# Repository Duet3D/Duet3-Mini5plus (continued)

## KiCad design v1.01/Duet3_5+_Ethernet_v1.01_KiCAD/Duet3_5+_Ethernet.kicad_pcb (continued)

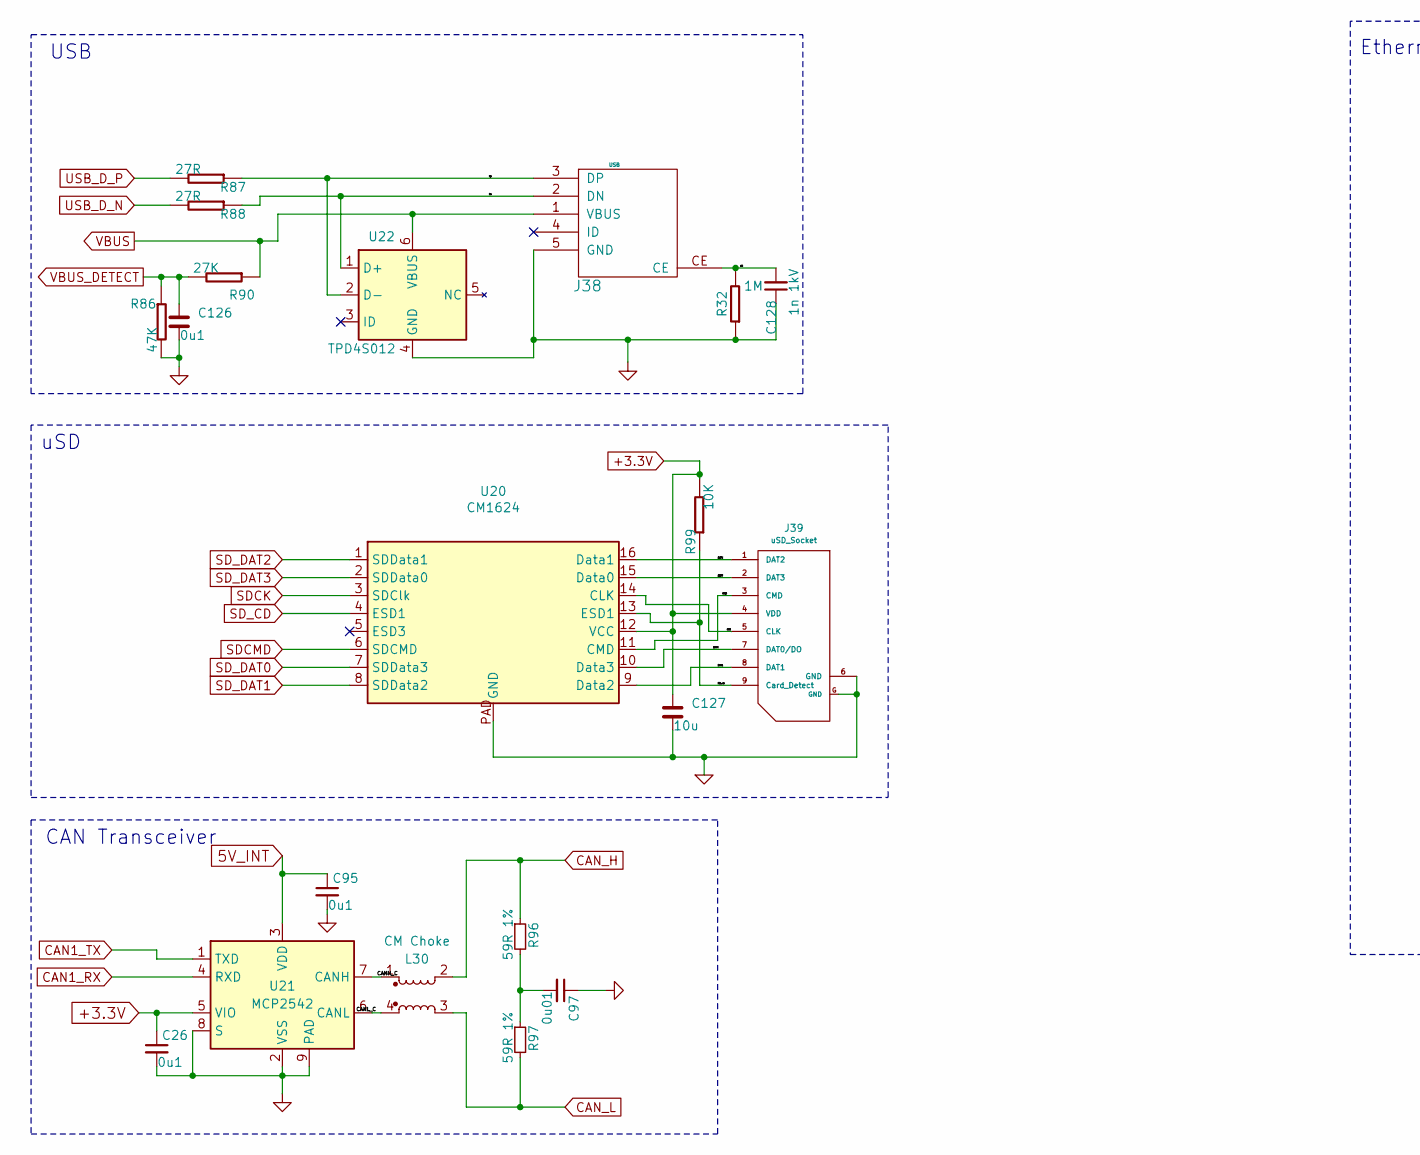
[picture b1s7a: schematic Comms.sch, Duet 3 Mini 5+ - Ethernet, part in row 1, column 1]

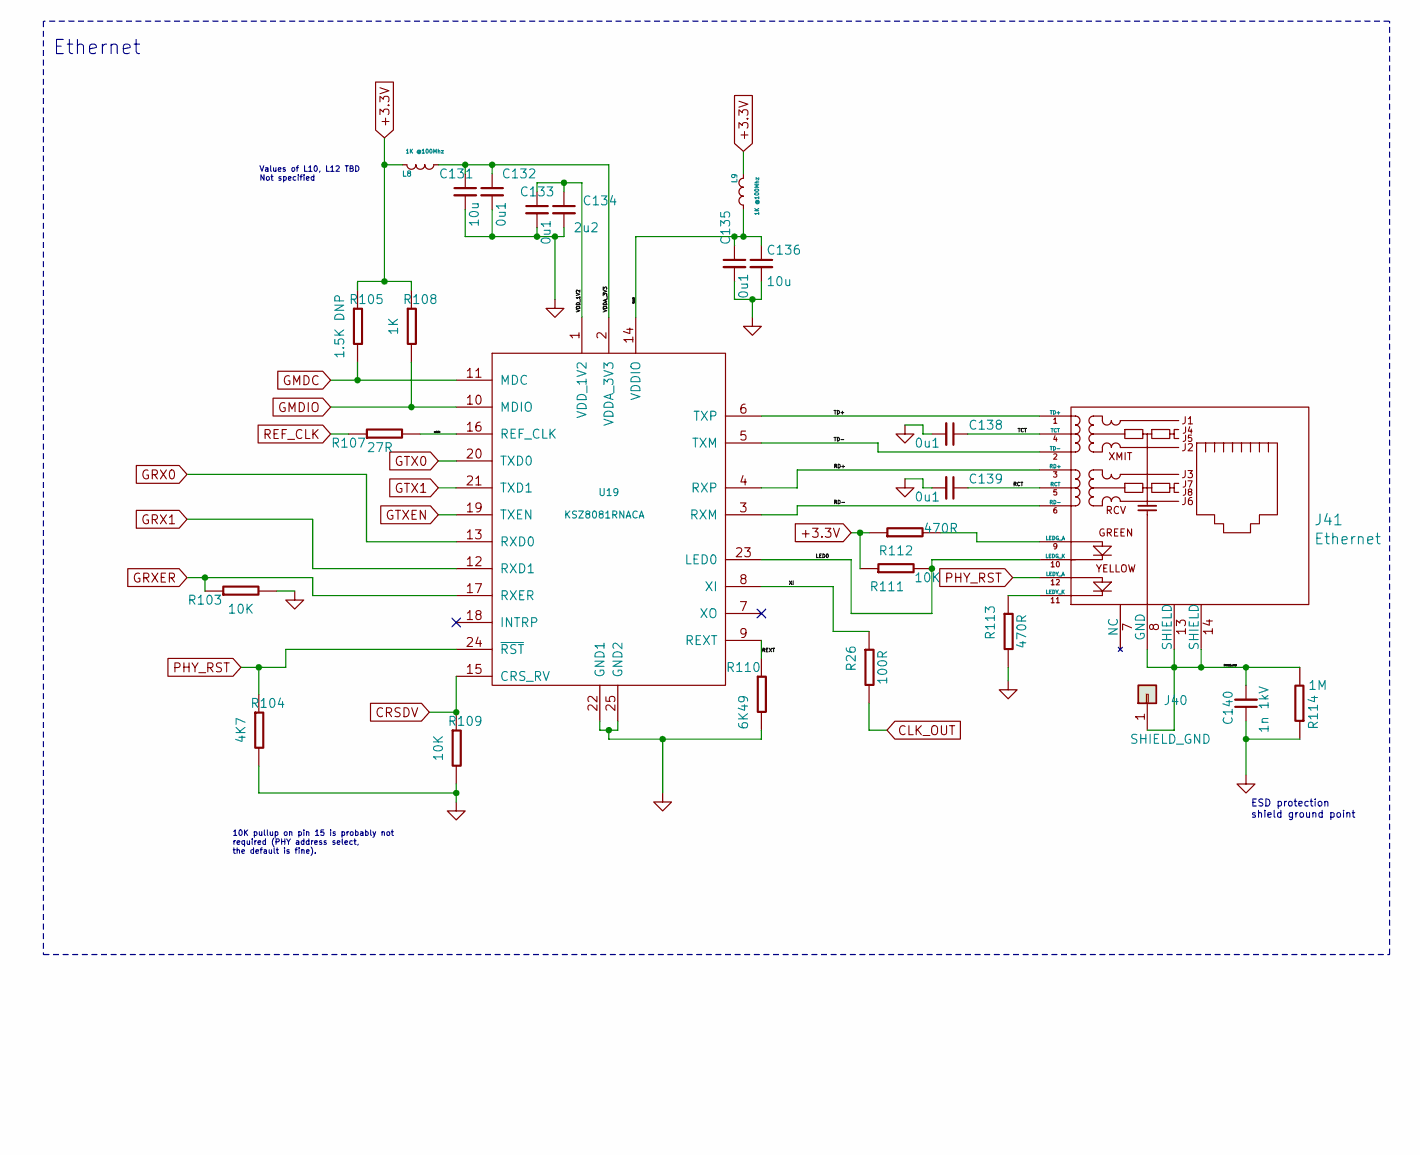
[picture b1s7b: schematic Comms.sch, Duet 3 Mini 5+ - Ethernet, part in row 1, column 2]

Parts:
C26, C95, C126, C132, C133, C135, C138, C139: 0u1; C_0402_1005Metric_Wbry; Part Number CL05A104KA5NNNC or similar
C97: 0u01; C_0402_1005Metric_Wbry; Part Number TMK105B7103KV-F
C127, C131, C136: 10u; C_0805_2012Metric; Part Number e.g CL21A106KQCLRNC
C128, C140: 1n 1kV; C_0805_2012Metric; Part Number CC0805KRX7RCBB102
C134: 2u2; C_0402_1005Metric_Wbry; Part Number LMK105BJ225KV-F or similar 10v+
J38: USB; uUSB_new; Part Number 10103594-0001LF
J39: uSD_Socket; uSD_SKT; Part Number 693071020811
J40: SHIELD_GND; 2.8mm_Spade_terminal; Part Number DNP - PC110D5
J41: Ethernet; RJ45+MAG; Part Number HR911105A
L8, L9: 1K @100Mhz; L_0603_1608Metric; Part Number BK1608HS102-T or PE-0603FB102ST or simi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
L30: CM Choke; Wurth_CM_Choke_744231121; Part Number 744231121 or SRF2012A-121YA
R26: 100R; R_0402_1005Metric_Wbry
R32, R114: 1M; R_0805_2012Metric; Part Number RMCF0805JT1M00
R86: 47K; R_0402_1005Metric_Wbry; Part Number RMCF0402FT47K0
R87, R88, R107: 27R; R_0402_1005Metric_Wbry; Part Number RC0402FR-0727RL
R90: 27K; R_0402_1005Metric_Wbry; Part Number RK73H1ETTP2702F
R96, R97: 59R 1%; R_0402_1005Metric_Wbry; Part Number RK73H1ETTP59R0F
R99, R103, R109, R111: 10K; R_0402_1005Metric_Wbry; Part Number RK73H1ETTP1002F
R104: 4K7; R_0402_1005Metric_Wbry; Part Number RK73H1ETTP4701F
R105: 1.5K DNP; R_0402_1005Metric_Wbry; Part Number DNP
R108: 1K; R_0402_1005Metric_Wbry; Part Number RK73H1ETTP1001F
R110: 6K49; R_0402_1005Metric_Wbry; Part Number RC0402FR-076K49L
R112, R113: 470R; R_0402_1005Metric_Wbry; Part Number RK73H1ETTP4700F
U19: KSZ8081RNACA; KSZ8081RNA _QFN-24-1EP_4x4mm_P0.5mm_EP2.6x2.6mm; Part Number KSZ8081RNACA
U20: CM1624; UDFN-16-1EP_1.35x3.3_P0.4_Duet3D; Part Number CM1624−08DE
U21: MCP2542; DFN-8-1EP_3x2mm_P0.5mm_EP1.3x1.5mm; Part Number MCP2542FDT-E/MNY
U22: TPD4S012; USON-6_1.45x1_TI_DRY06mm; Part Number TPD4S012DRYR

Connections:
5V_INT: C95.1, U21.3 (VDD); also elsewhere on the board
+3.3V: C26.1, C127.1, J39.4 (VDD), L8.1 (A), L9.1 (A), R99.2, R105.1, R108.1, R111.1, R112.1, U20.12 (VCC), U21.5 (VIO); also elsewhere on the board
/Comms/CANH_C: L30.1, U21.7 (CANH)
/Comms/CANL_C: L30.4, U21.6 (CANL)
/Comms/CE: C128.2, J38.CE, R32.2
/Comms/CLK: J39.5 (CLK), U20.14 (CLK)
/Comms/CMD: J39.3 (CMD), U20.11 (CMD)
/Comms/DAT0: J39.7 (DAT0/DO), U20.10 (Data3)
/Comms/DAT1: J39.8 (DAT1), U20.9 (Data2)
/Comms/DAT2: J39.1 (DAT2), U20.16 (Data1)
/Comms/DAT3: J39.2 (DAT3), U20.15 (Data0)
/Comms/LED0: J41.10 (LEDG_K), R111.2, U19.23 (LED0)
/Comms/RCT: C139.1, J41.5 (RCT)
/Comms/RD+: J41.3 (RD+), U19.4 (RXP)
/Comms/RD-: J41.6 (RD-), U19.3 (RXM)
/Comms/REXT: R110.1, U19.9 (REXT)
/Comms/SD_cd: J39.9 (Card_Detect), R99.1, U20.13 (ESD1)
/Comms/SHIELD_GND: C140.2, J40.1, J41.8 (GND), J41.13 (SHIELD), J41.14 (SHIELD), R114.2
/Comms/TCT: C138.1, J41.4 (TCT)
/Comms/TD+: J41.1 (TD+), U19.6 (TXP)
/Comms/TD-: J41.2 (TD-), U19.5 (TXM)
/Comms/VDDA_3V3: C131.1, C132.1, L8.2 (B), U19.2 (VDDA_3V3)
/Comms/VDDIO: C135.1, C136.1, L9.2 (B), U19.14 (VDDIO)
/Comms/VDD_1V2: C133.1, C134.1, U19.1 (VDD_1V2)
/Comms/XI: R26.1, U19.8 (XI)
/Comms/dn: J38.2 (DN), R88.1, U22.1 (D+)
/Comms/dp: J38.3 (DP), R87.1, U22.2 (D-)
/Comms/refclk: R107.2, U19.16 (REF_CLK)
CAN1_RX: U21.4 (RXD); also elsewhere on the board
CAN1_TX: U21.1 (TXD); also elsewhere on the board
CAN_H: L30.2, R96.1; also elsewhere on the board
CAN_L: L30.3, R97.2; also elsewhere on the board
CLK_OUT: R26.2; also elsewhere on the board
CRSDV: R109.1, U19.15 (CRS_RV); also elsewhere on the board
GMDC: R105.2, U19.11 (MDC); also elsewhere on the board
GMDIO: R108.2, U19.10 (MDIO); also elsewhere on the board
GND: C26.2, C95.2, C97.1, C126.2, C127.2, C128.1, C131.2, C132.2, C133.2, C134.2, C135.2, C136.2, C138.2, C139.2, C140.1, J38.5 (GND), J39.6 (GND), J39.G (GND), R32.1, R86.2, R103.2, R104.2, R109.2, R110.2, R113.2, R114.1, U19.22 (GND1), U19.25 (GND2), U20.PAD (GND), U21.2 (VSS), U21.8 (S), U21.9 (PAD), U22.4 (GND); also elsewhere on the board
GRX0: U19.13 (RXD0); also elsewhere on the board
GRX1: U19.12 (RXD1); also elsewhere on the board
GRXER: R103.1, U19.17 (RXER); also elsewhere on the board
GTX0: U19.20 (TXD0); also elsewhere on the board
GTX1: U19.21 (TXD1); also elsewhere on the board
GTXEN: U19.19 (TXEN); also elsewhere on the board
unnamed: C97.2, R96.2, R97.1
unnamed: J41.9 (LEDG_A), R112.2
unnamed: J41.11 (LEDY_K), R113.1
PHY_RST: J41.12 (LEDY_A), R104.1, U19.24 (~RST); also elsewhere on the board
REF_CLK: R107.1; also elsewhere on the board
SDCK: U20.3 (SDClk); also elsewhere on the board
SDCMD: U20.6 (SDCMD); also elsewhere on the board
SD_CD: U20.4 (ESD1); also elsewhere on the board
SD_DAT0: U20.7 (SDData3); also elsewhere on the board
SD_DAT1: U20.8 (SDData2); also elsewhere on the board
SD_DAT2: U20.1 (SDData1); also elsewhere on the board
SD_DAT3: U20.2 (SDData0); also elsewhere on the board
USB_D_N: R88.2; also elsewhere on the board
USB_D_P: R87.2; also elsewhere on the board
VBUS: J38.1 (VBUS), R90.1, U22.6 (VBUS); also elsewhere on the board
VBUS_DETECT: C126.1, R86.1, R90.2; also elsewhere on the board

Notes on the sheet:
USB
ESD protection shield ground point
Ethernet
Values of L10, L12 TBD Not specified
uSD
10K pullup on pin 15 is probably not required (PHY address select, the default is fine).
CAN Transceiver

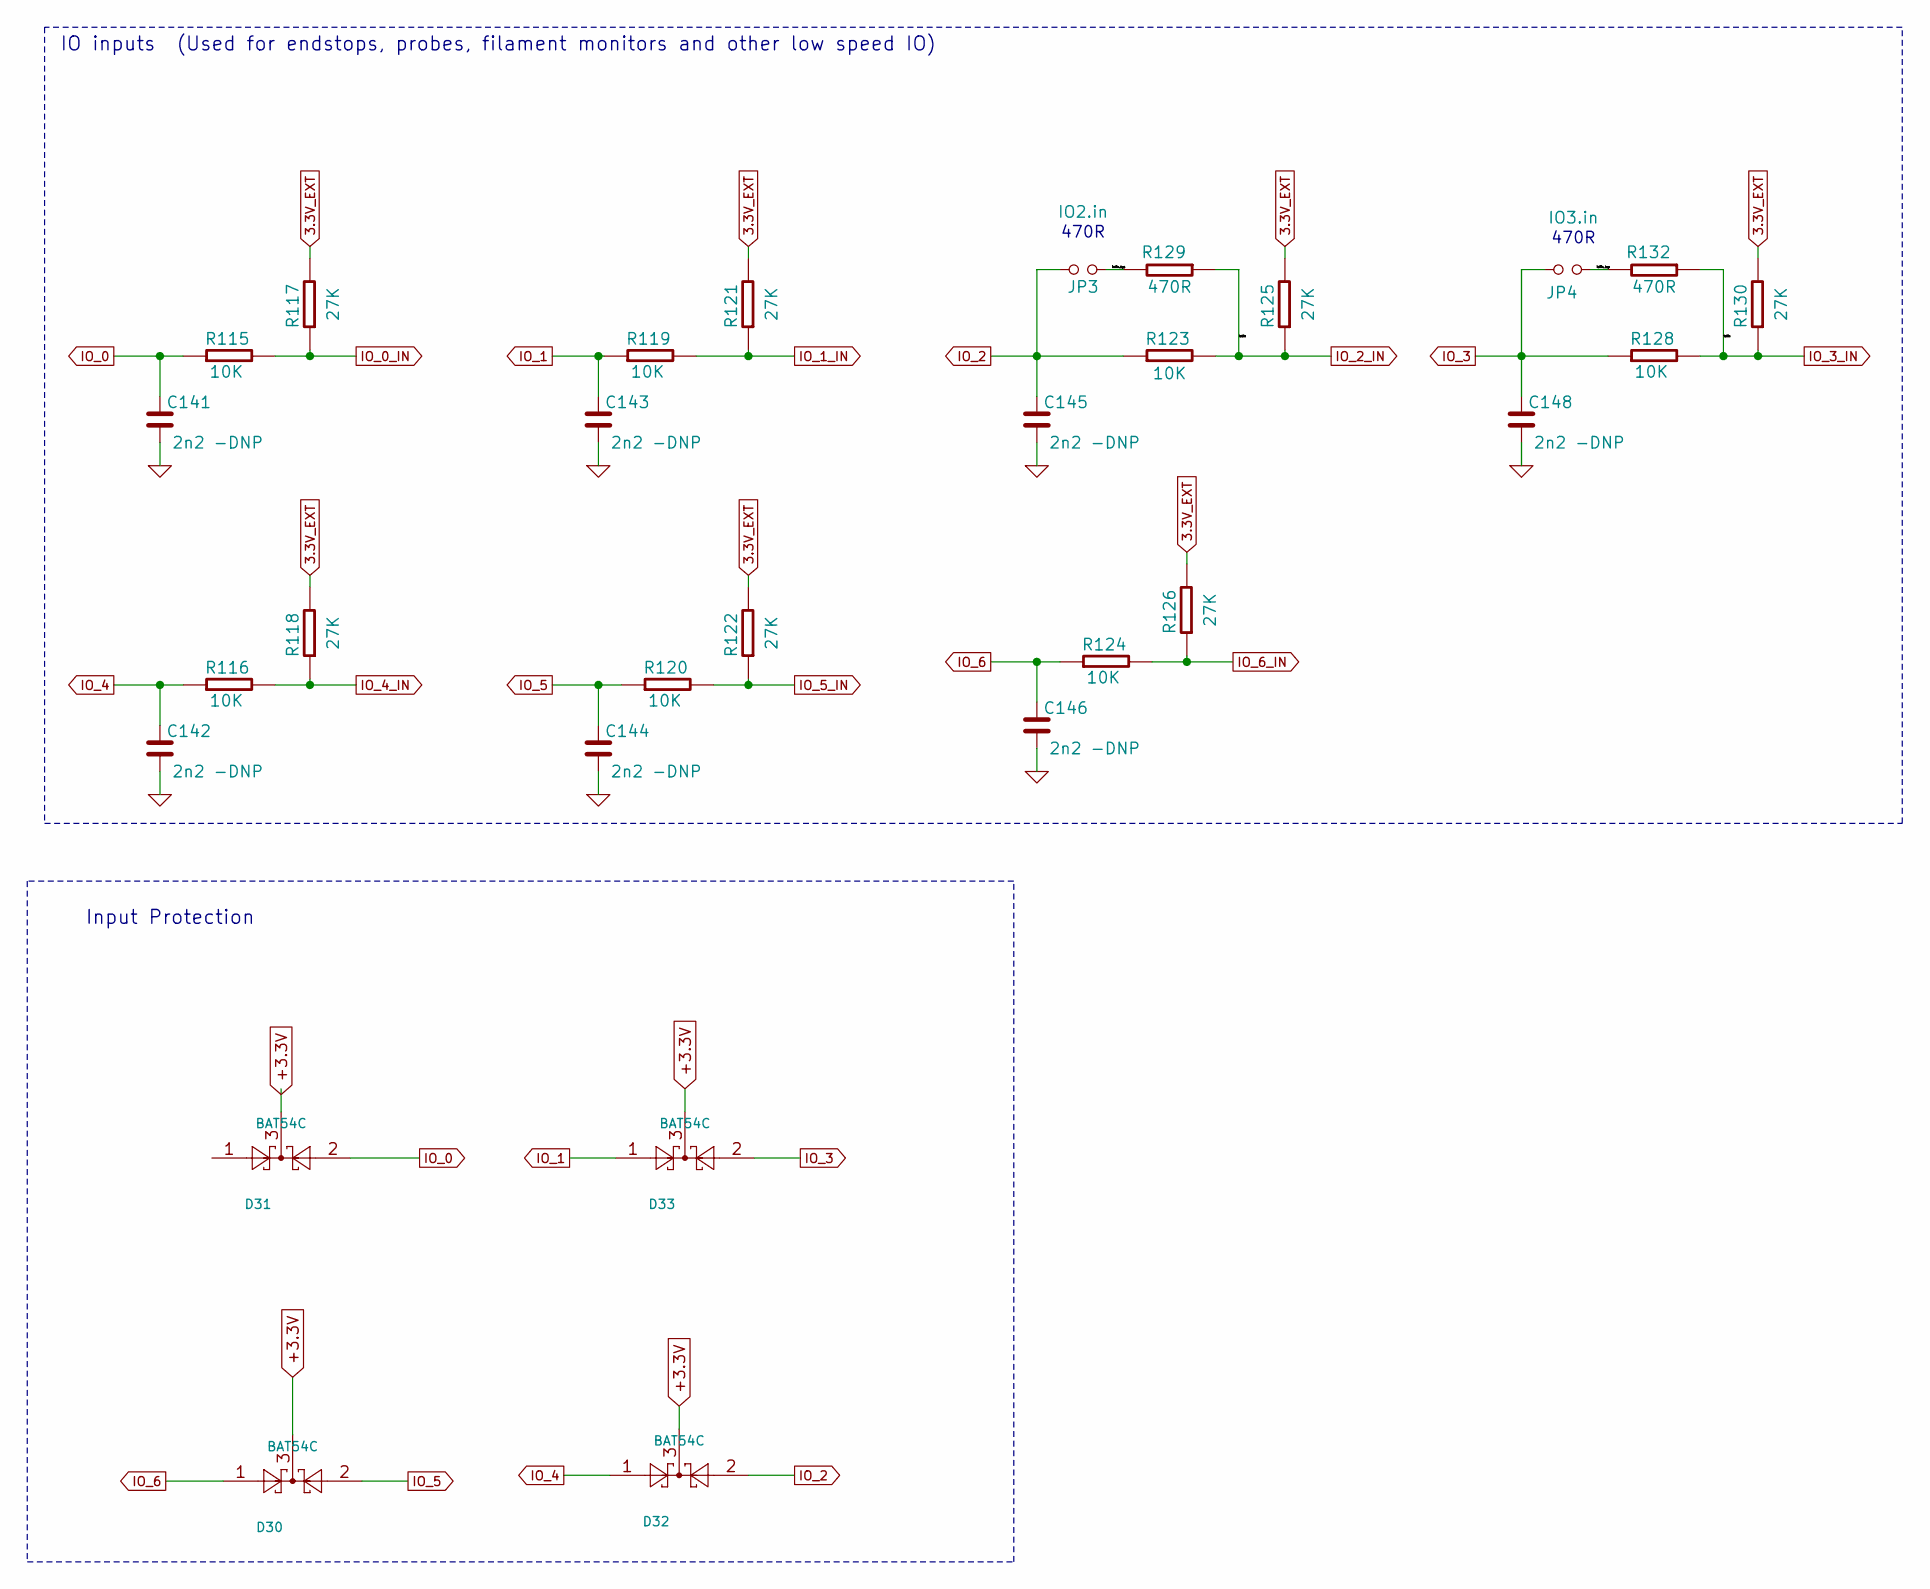
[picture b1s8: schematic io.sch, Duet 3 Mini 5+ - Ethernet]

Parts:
C141, C142, C143, C144, C145, C146, C148: 2n2 -DNP; C_0402_1005Metric_Wbry; Part Number DNP
D30, D31, D32, D33: BAT54C; SOT-23; Part Number BAT54C-7-F
JP3: IO2.in; PinHeader_1x02_P2.54mm_Vertical; Part Number THS-02-R
JP4: IO3.in; PinHeader_1x02_P2.54mm_Vertical; Part Number THS-02-R
R115, R116, R119, R120, R123, R124, R128: 10K; R_0402_1005Metric_Wbry; Part Number RK73H1ETTP1002F
R117, R118, R121, R122, R125, R126, R130: 27K; R_0402_1005Metric_Wbry; Part Number RK73H1ETTP2702F
R129, R132: 470R; R_0402_1005Metric_Wbry; Part Number RK73H1ETTP4700F

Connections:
3.3V_EXT: R117.2, R118.2, R121.2, R122.2, R125.2, R126.2, R130.2; also elsewhere on the board
+3.3V: D30.3, D31.3, D32.3, D33.3; also elsewhere on the board
/IO/io2in_byp: JP3.2, R129.2
/IO/io3in_byp: JP4.2, R132.2
GND: C141.2, C142.2, C143.2, C144.2, C145.2, C146.2, C148.2; also elsewhere on the board
IO_0: C141.1, D31.2, R115.1; also elsewhere on the board
IO_0_IN: R115.2, R117.1; also elsewhere on the board
IO_1: C143.1, D33.1, R119.1; also elsewhere on the board
IO_1_IN: R119.2, R121.1; also elsewhere on the board
IO_2: C145.1, D32.2, JP3.1, R123.1; also elsewhere on the board
IO_2_IN: R123.2, R125.1, R129.1; also elsewhere on the board
IO_3: C148.1, D33.2, JP4.1, R128.1; also elsewhere on the board
IO_3_IN: R128.2, R130.1, R132.1; also elsewhere on the board
IO_4: C142.1, D32.1, R116.1; also elsewhere on the board
IO_4_IN: R116.2, R118.1; also elsewhere on the board
IO_5: C144.1, D30.2, R120.1; also elsewhere on the board
IO_5_IN: R120.2, R122.1; also elsewhere on the board
IO_6: C146.1, D30.1, R124.1; also elsewhere on the board
IO_6_IN: R124.2, R126.1; also elsewhere on the board

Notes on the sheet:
IO inputs (Used for endstops, probes, filament monitors and other low speed IO)
Input Protection
470R

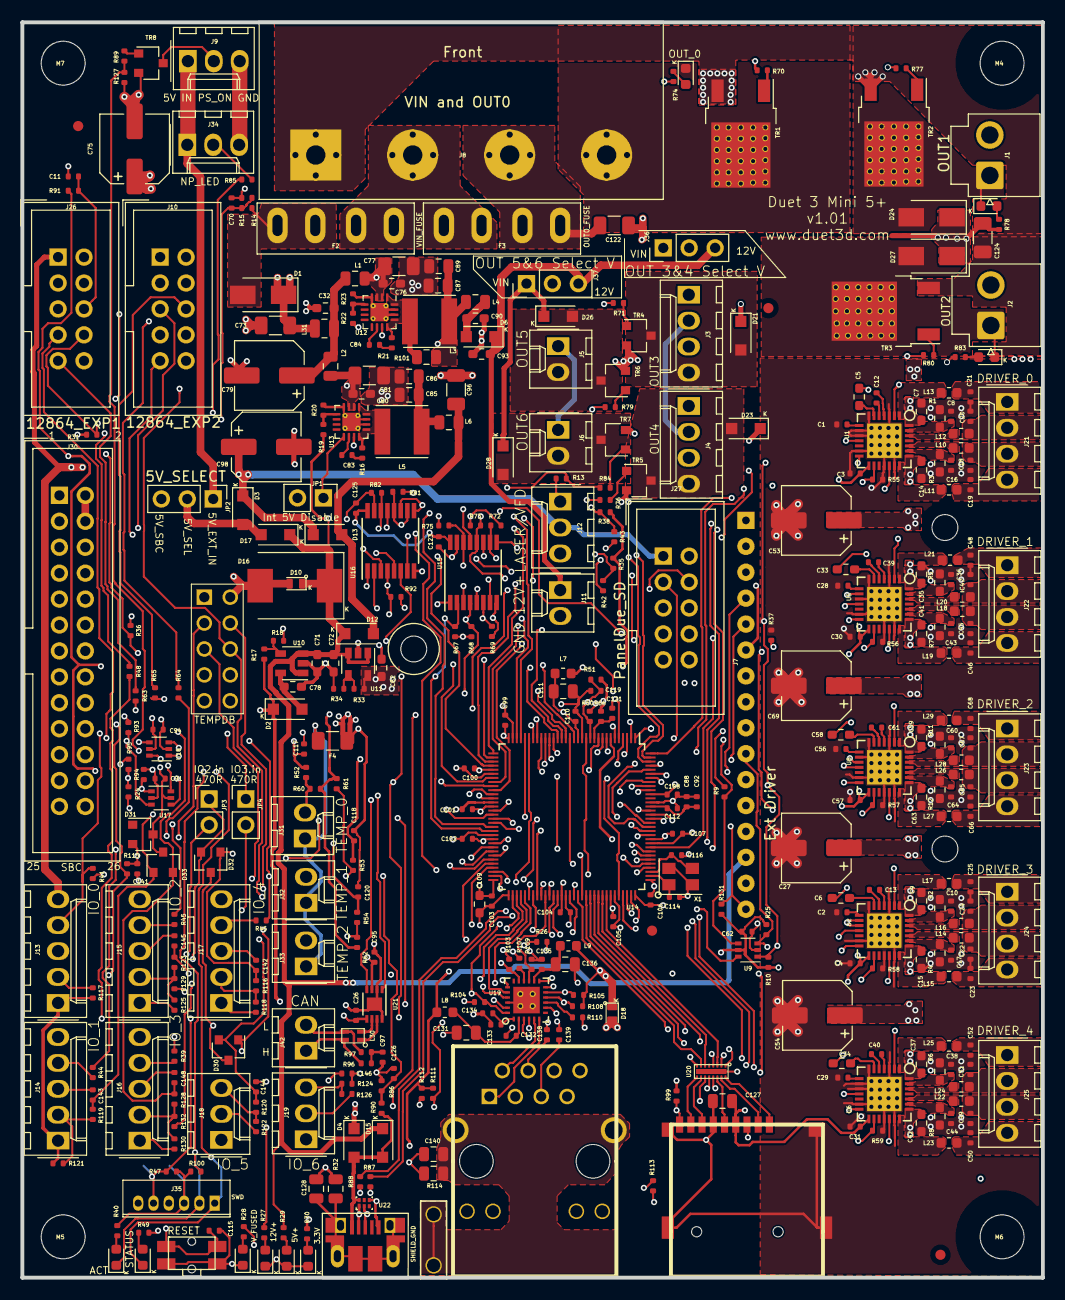
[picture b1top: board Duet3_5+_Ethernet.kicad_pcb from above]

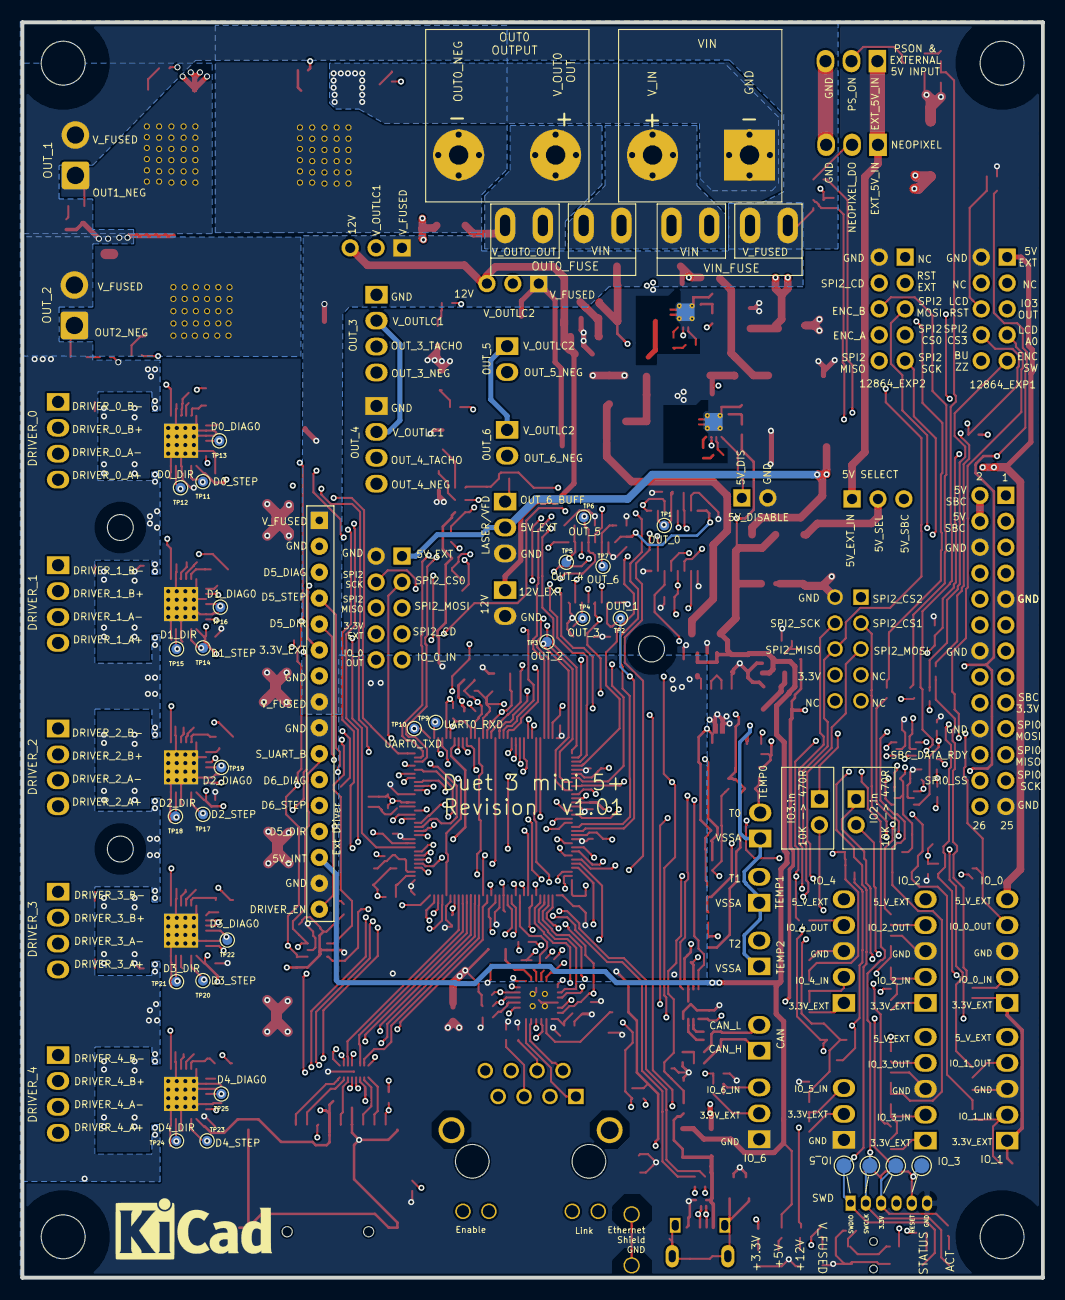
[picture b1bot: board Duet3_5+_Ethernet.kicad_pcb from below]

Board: 4 copper layers, 100.0 x 123.0 mm, 447 parts (29 on the bottom side), 310 nets.

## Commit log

2021-05-04 Create LICENSE
2021-05-04 Add STEPs files and Schematics
2021-08-02 Fixed corrupted STEP zip files
2021-08-02 Mini 5+ v1.01 Schematics and STEP files
2021-08-05 Added Mini 2+ Schematic & Step File
2022-02-17 Documentation Link Updates
2022-03-31 Mini 5+ v1.01 KiCAD files
2022-05-20 added the cache files
